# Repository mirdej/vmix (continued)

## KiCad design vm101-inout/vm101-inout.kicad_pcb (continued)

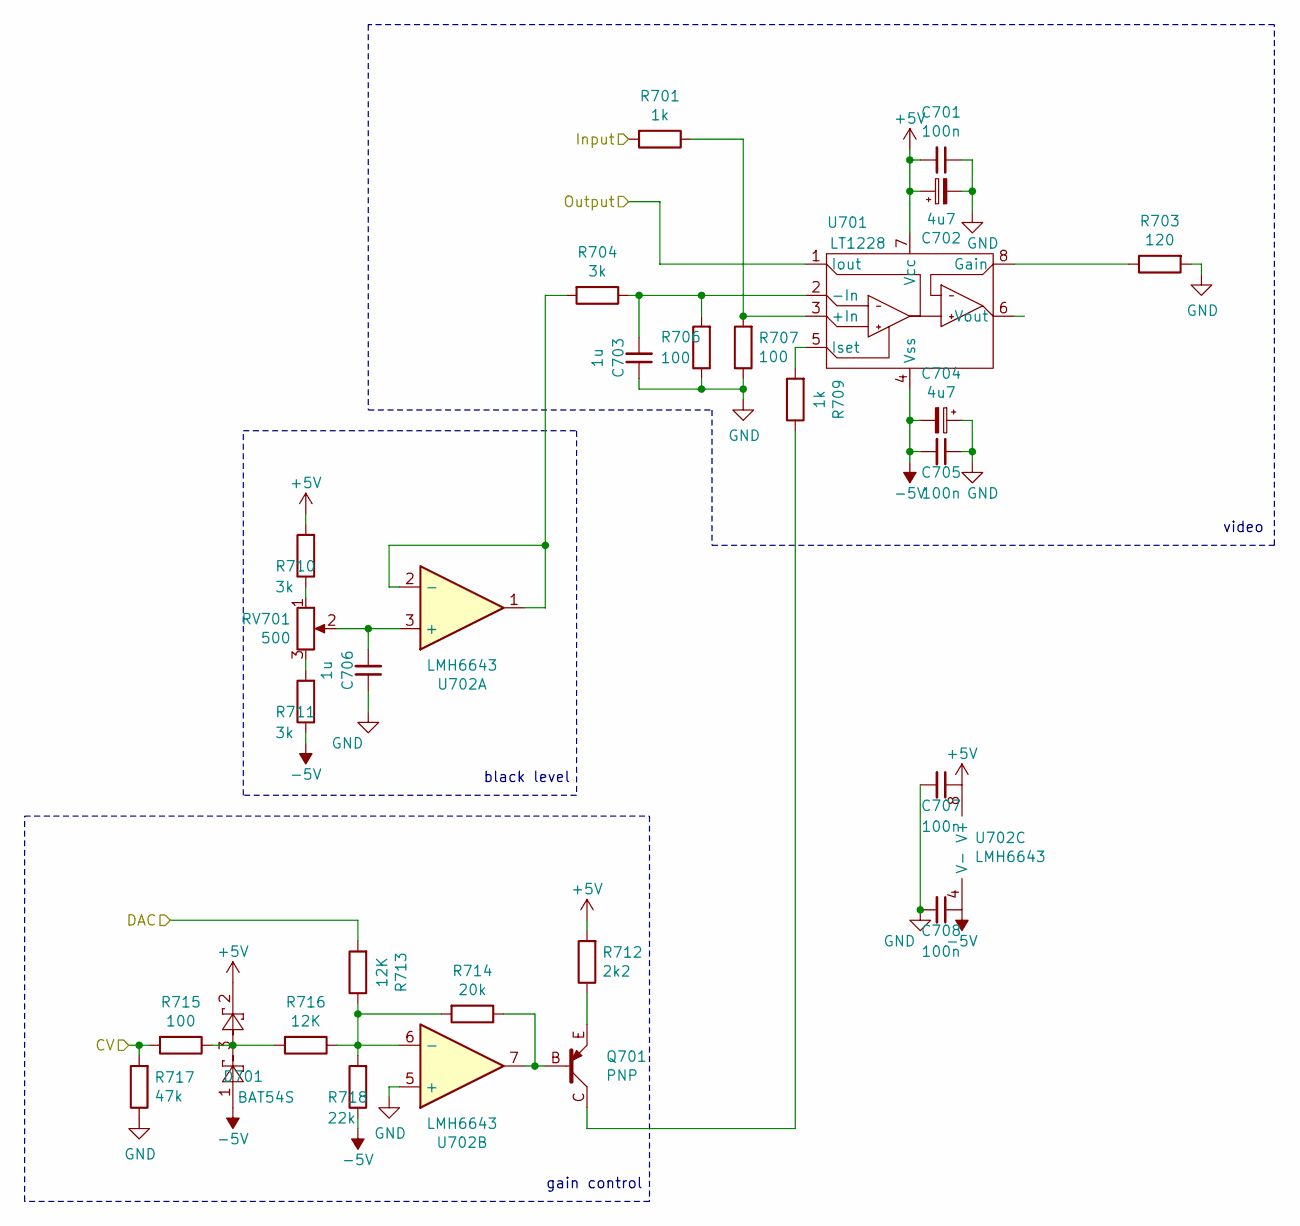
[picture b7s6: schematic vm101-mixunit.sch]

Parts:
C1001, C1005, C1007, C1008: 100n; C_0603_1608Metric_Pad1.05x0.95mm_HandSolder
C1002, C1004: 4u7; CP_EIA-3528-21_Kemet-B_Pad1.50x2.35mm_HandSolder
C1003, C1006: 1u; C_0603_1608Metric_Pad1.05x0.95mm_HandSolder
D1001: BAT54S; SOT-23
Q1001: PNP; SOT-23_BEC
R1001, R1009: 1k; R_0805_2012Metric_Pad1.15x1.40mm_HandSolder
R1003: 120; R_0805_2012Metric_Pad1.15x1.40mm_HandSolder
R1004, R1010, R1011: 3k; R_0805_2012Metric_Pad1.15x1.40mm_HandSolder
R1006, R1007, R1015: 100; R_0805_2012Metric_Pad1.15x1.40mm_HandSolder
R1012: 2k2; R_0805_2012Metric_Pad1.15x1.40mm_HandSolder
R1013, R1016: 12K; R_0805_2012Metric_Pad1.15x1.40mm_HandSolder
R1014: 20k; R_0805_2012Metric_Pad1.15x1.40mm_HandSolder
R1017: 47k; R_0805_2012Metric_Pad1.15x1.40mm_HandSolder
R1018: 22k; R_0805_2012Metric_Pad1.15x1.40mm_HandSolder
RV1001: 500; Potentiometer_Bourns_3006P_Horizontal
U1001: LT1228; SOIC-8_3.9x4.9mm_P1.27mm
U1002: LMH6643; SOIC-8_3.9x4.9mm_P1.27mm

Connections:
+5V: C1001.2, C1002.1, C1007.1, D1001.2, R1010.2, R1012.2, U1001.7 (Vcc), U1002.8 (V+); also elsewhere on the board
-5V: C1004.2, C1005.2, C1008.1, D1001.1, R1011.1, R1018.1, U1001.4 (Vss), U1002.4 (V-); also elsewhere on the board
/Mixer/dac_a: R1013.2; also elsewhere on the board
/from_eq: R1001.2; also elsewhere on the board
GND: C1001.1, C1002.2, C1003.1, C1004.1, C1005.1, C1006.1, C1007.2, C1008.2, R1003.2, R1006.1, R1007.1, R1017.1, U1002.5 (+); also elsewhere on the board
unnamed: C1003.2, R1004.1, R1006.2, U1001.2 (-In)
unnamed: C1006.2, RV1001.2, U1002.3 (+)
unnamed: D1001.3, R1015.1, R1016.2
unnamed: Q1001.B, R1014.1, U1002.7
unnamed: Q1001.C, R1009.1
unnamed: Q1001.E, R1012.1
unnamed: R1001.1, R1007.2, U1001.3 (+In)
unnamed: R1003.1, U1001.8 (Gain)
unnamed: R1004.2, U1002.1, U1002.2 (-)
unnamed: R1009.2, U1001.5 (Iset)
unnamed: R1010.1, RV1001.1
unnamed: R1011.2, RV1001.3
unnamed: R1013.1, R1014.2, R1016.1, R1018.2, U1002.6 (-)
cv_a: R1015.2, R1017.2; also elsewhere on the board
out_a: U1001.1 (Iout); also elsewhere on the board

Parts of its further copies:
C701, C705, C707, C708, C801, C805, C807, C808, C901, C905, C907, C908: 100n; C_0603_1608Metric_Pad1.05x0.95mm_HandSolder
C702, C704, C802, C804, C902, C904: 4u7; CP_EIA-3528-21_Kemet-B_Pad1.50x2.35mm_HandSolder
C703, C706, C803, C806, C903, C906: 1u; C_0603_1608Metric_Pad1.05x0.95mm_HandSolder
D701, D801, D901: BAT54S; SOT-23
Q701, Q801, Q901: PNP; SOT-23_BEC
R701, R709, R801, R809, R901, R909: 1k; R_0805_2012Metric_Pad1.15x1.40mm_HandSolder
R703, R803, R903: 120; R_0805_2012Metric_Pad1.15x1.40mm_HandSolder
R704, R710, R711, R804, R810, R811, R904, R910, R911: 3k; R_0805_2012Metric_Pad1.15x1.40mm_HandSolder
R706, R707, R715, R806, R807, R815, R906, R907, R915: 100; R_0805_2012Metric_Pad1.15x1.40mm_HandSolder
R712, R812, R912: 2k2; R_0805_2012Metric_Pad1.15x1.40mm_HandSolder
R713, R716, R813, R816, R913, R916: 12K; R_0805_2012Metric_Pad1.15x1.40mm_HandSolder
R714, R814, R914: 20k; R_0805_2012Metric_Pad1.15x1.40mm_HandSolder
R717, R817, R917: 47k; R_0805_2012Metric_Pad1.15x1.40mm_HandSolder
R718, R818, R918: 22k; R_0805_2012Metric_Pad1.15x1.40mm_HandSolder
RV701, RV801, RV901: 500; Potentiometer_Bourns_3006P_Horizontal
U701, U801, U901: LT1228; SOIC-8_3.9x4.9mm_P1.27mm
U702, U802, U902: LMH6643; SOIC-8_3.9x4.9mm_P1.27mm

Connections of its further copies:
+5V: C701.2, C702.1, C707.1, C801.2, C802.1, C807.1, C901.2, C902.1, C907.1, D701.2, D801.2, D901.2, R710.2, R712.2, R810.2, R812.2, R910.2, R912.2, U701.7 (Vcc), U702.8 (V+), U801.7 (Vcc), U802.8 (V+), U901.7 (Vcc), U902.8 (V+); also elsewhere on the board
-5V: C704.2, C705.2, C708.1, C804.2, C805.2, C808.1, C904.2, C905.2, C908.1, D701.1, D801.1, D901.1, R711.1, R718.1, R811.1, R818.1, R911.1, R918.1, U701.4 (Vss), U702.4 (V-), U801.4 (Vss), U802.4 (V-), U901.4 (Vss), U902.4 (V-); also elsewhere on the board
/Mixer/dac_b: R713.2; also elsewhere on the board
/Mixer/dac_c: R813.2; also elsewhere on the board
/Mixer/dac_d: R913.2; also elsewhere on the board
/from_eq: R701.2, R801.2, R901.2; also elsewhere on the board
GND: C701.1, C702.2, C703.1, C704.1, C705.1, C706.1, C707.2, C708.2, C801.1, C802.2, C803.1, C804.1, C805.1, C806.1, C807.2, C808.2, C901.1, C902.2, C903.1, C904.1, C905.1, C906.1, C907.2, C908.2, R703.2, R706.1, R707.1, R717.1, R803.2, R806.1, R807.1, R817.1, R903.2, R906.1, R907.1, R917.1, U702.5 (+), U802.5 (+), U902.5 (+); also elsewhere on the board
unnamed: C703.2, R704.1, R706.2, U701.2 (-In)
unnamed: C706.2, RV701.2, U702.3 (+)
unnamed: C803.2, R804.1, R806.2, U801.2 (-In)
unnamed: C806.2, RV801.2, U802.3 (+)
unnamed: C903.2, R904.1, R906.2, U901.2 (-In)
unnamed: C906.2, RV901.2, U902.3 (+)
unnamed: D701.3, R715.1, R716.2
unnamed: D801.3, R815.1, R816.2
unnamed: D901.3, R915.1, R916.2
unnamed: Q701.B, R714.1, U702.7
unnamed: Q701.C, R709.1
unnamed: Q701.E, R712.1
unnamed: Q801.B, R814.1, U802.7
unnamed: Q801.C, R809.1
unnamed: Q801.E, R812.1
unnamed: Q901.B, R914.1, U902.7
unnamed: Q901.C, R909.1
unnamed: Q901.E, R912.1
unnamed: R701.1, R707.2, U701.3 (+In)
unnamed: R703.1, U701.8 (Gain)
unnamed: R704.2, U702.1, U702.2 (-)
unnamed: R709.2, U701.5 (Iset)
unnamed: R710.1, RV701.1
unnamed: R711.2, RV701.3
unnamed: R713.1, R714.2, R716.1, R718.2, U702.6 (-)
unnamed: R801.1, R807.2, U801.3 (+In)
unnamed: R803.1, U801.8 (Gain)
unnamed: R804.2, U802.1, U802.2 (-)
unnamed: R809.2, U801.5 (Iset)
unnamed: R810.1, RV801.1
unnamed: R811.2, RV801.3
unnamed: R813.1, R814.2, R816.1, R818.2, U802.6 (-)
unnamed: R901.1, R907.2, U901.3 (+In)
unnamed: R903.1, U901.8 (Gain)
unnamed: R904.2, U902.1, U902.2 (-)
unnamed: R909.2, U901.5 (Iset)
unnamed: R910.1, RV901.1
unnamed: R911.2, RV901.3
unnamed: R913.1, R914.2, R916.1, R918.2, U902.6 (-)
cv_b: R715.2, R717.2; also elsewhere on the board
cv_c: R815.2, R817.2; also elsewhere on the board
cv_d: R915.2, R917.2; also elsewhere on the board
out_b: U701.1 (Iout); also elsewhere on the board
out_c: U801.1 (Iout); also elsewhere on the board
out_d: U901.1 (Iout); also elsewhere on the board

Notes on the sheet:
black level
gain control
video

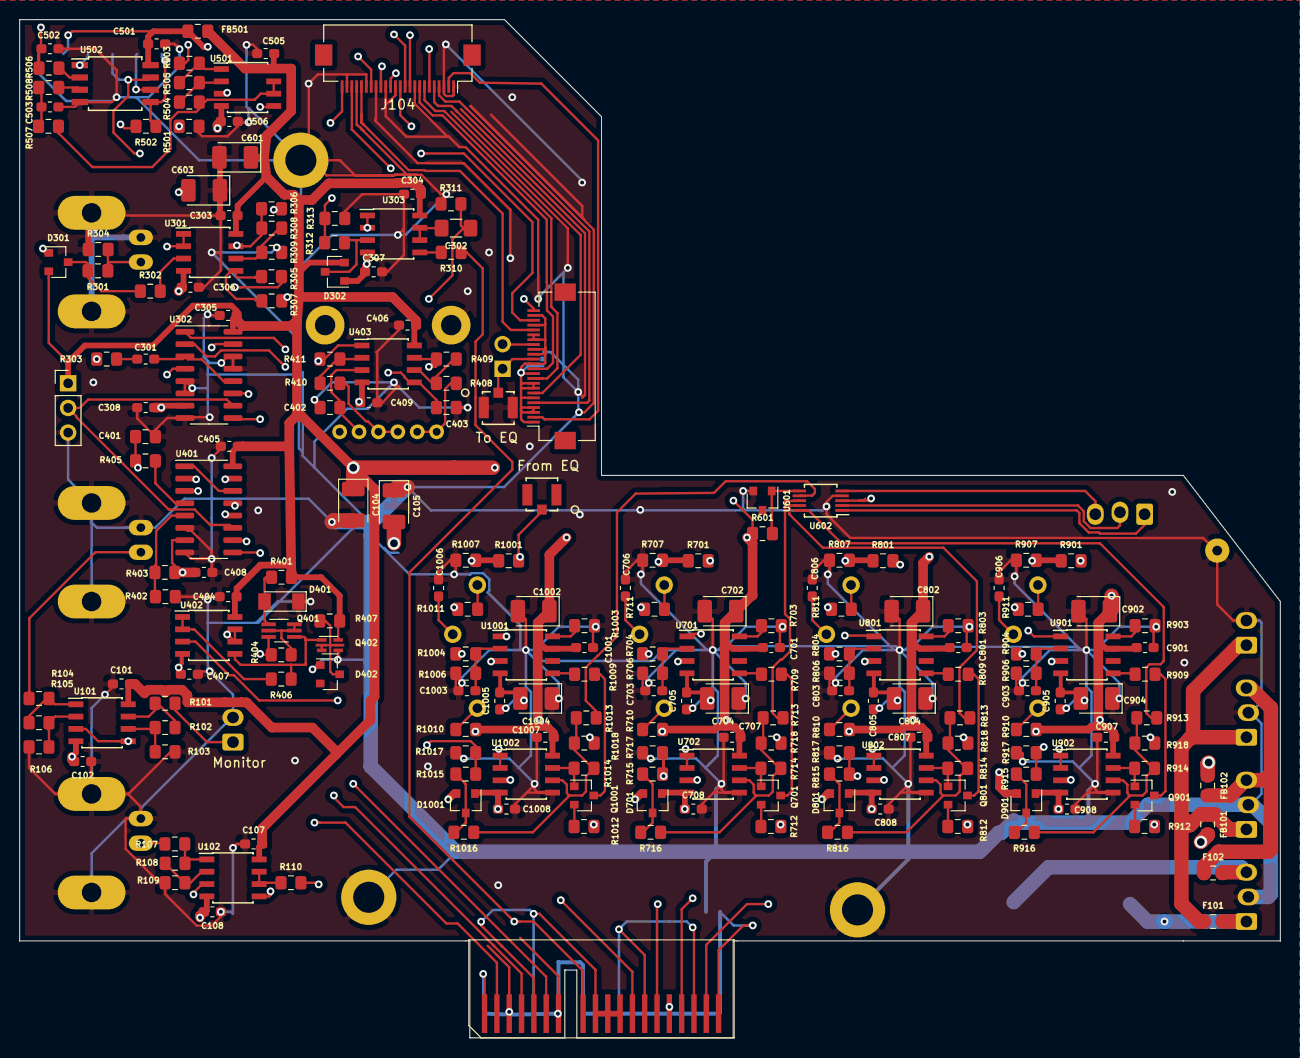
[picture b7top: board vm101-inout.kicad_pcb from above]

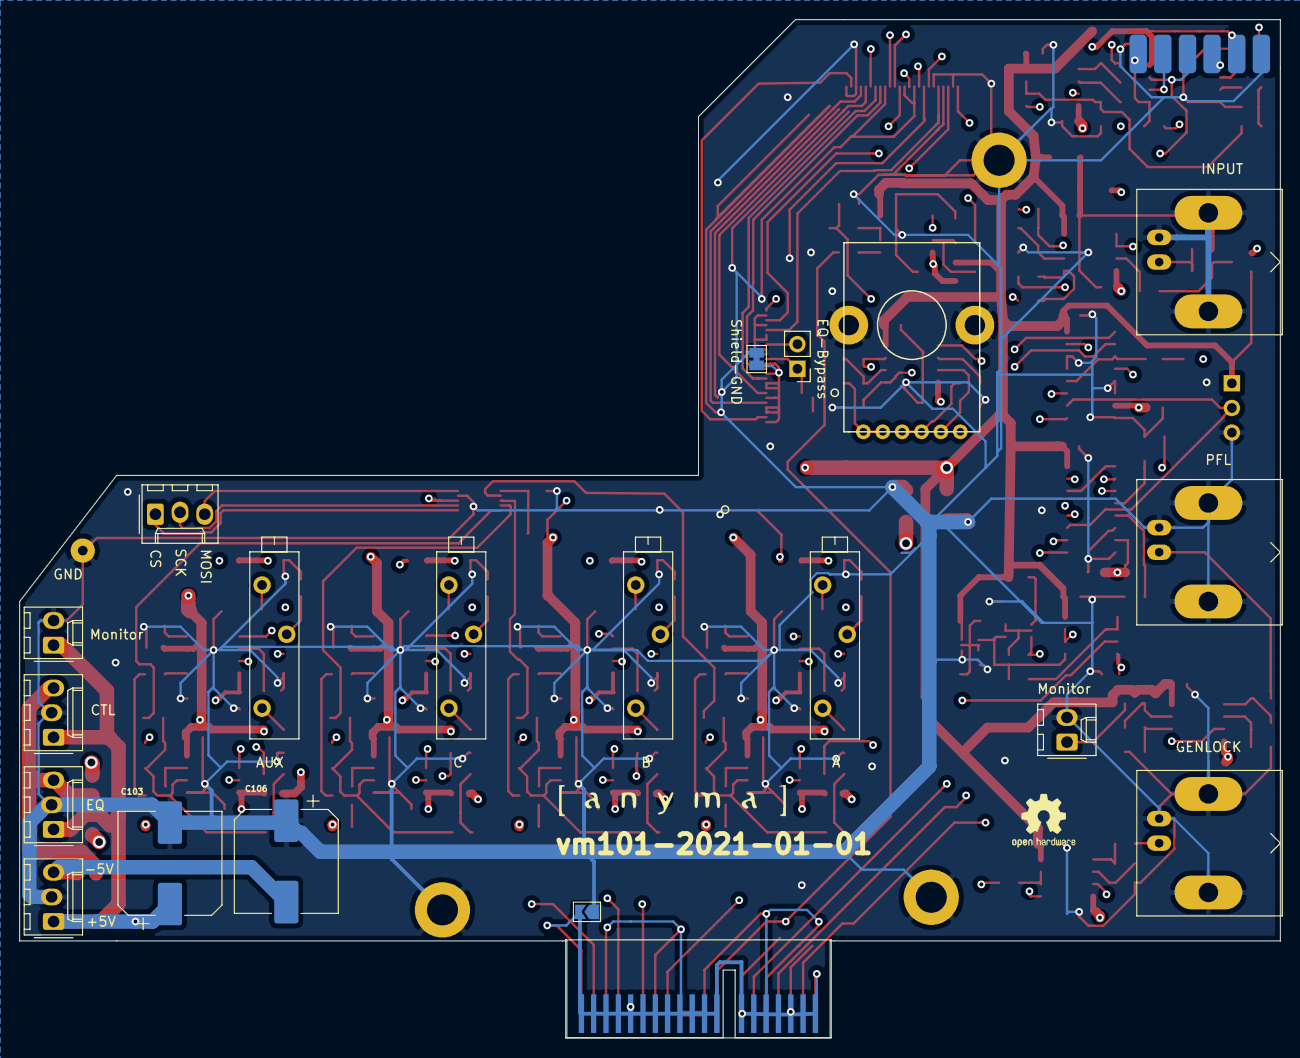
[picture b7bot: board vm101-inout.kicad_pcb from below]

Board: 4 copper layers, 130.0 x 105.0 mm, 236 parts (22 on the bottom side), 149 nets.

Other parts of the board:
U1003: LOGO; logo_anyma
U1004: LOGO; OSHW-Logo2_7.3x6mm_SilkScreen
